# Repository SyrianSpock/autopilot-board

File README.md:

Speedy, the nanocopter
======================

The aim of this project is to design a board enabling the control of a small quadrotor (nanocopter) that can be tracked by external visual sensors.

### Specifications
* Cortex M4 MCU
* Four infrared LEDs on each side of the board for IR vision tracking. Each side can be controlled separately.
* Two full H bridges: one half bridge per motor to allow active braking of the motors.
* IMU:
    - MPU9250 (9 axis): accelerometer, gyroscope and magnetometer
    - MS5611 barometer
* Ground distance sensor:
    - ST VL53L0X for landing / ground approach
* Telemetry module:
    - ESP12E for telemetry and telecommand through WiFi
* USB interface (for DFU programming / serial interface) and power/charging
* Battery management unit
	- Monitor battery (current, voltage)
	- Supply power to the board from a LiPo (1S) input
	- Recharge the battery through USB

### PCB

The 40mm x 40mm board is rendered below

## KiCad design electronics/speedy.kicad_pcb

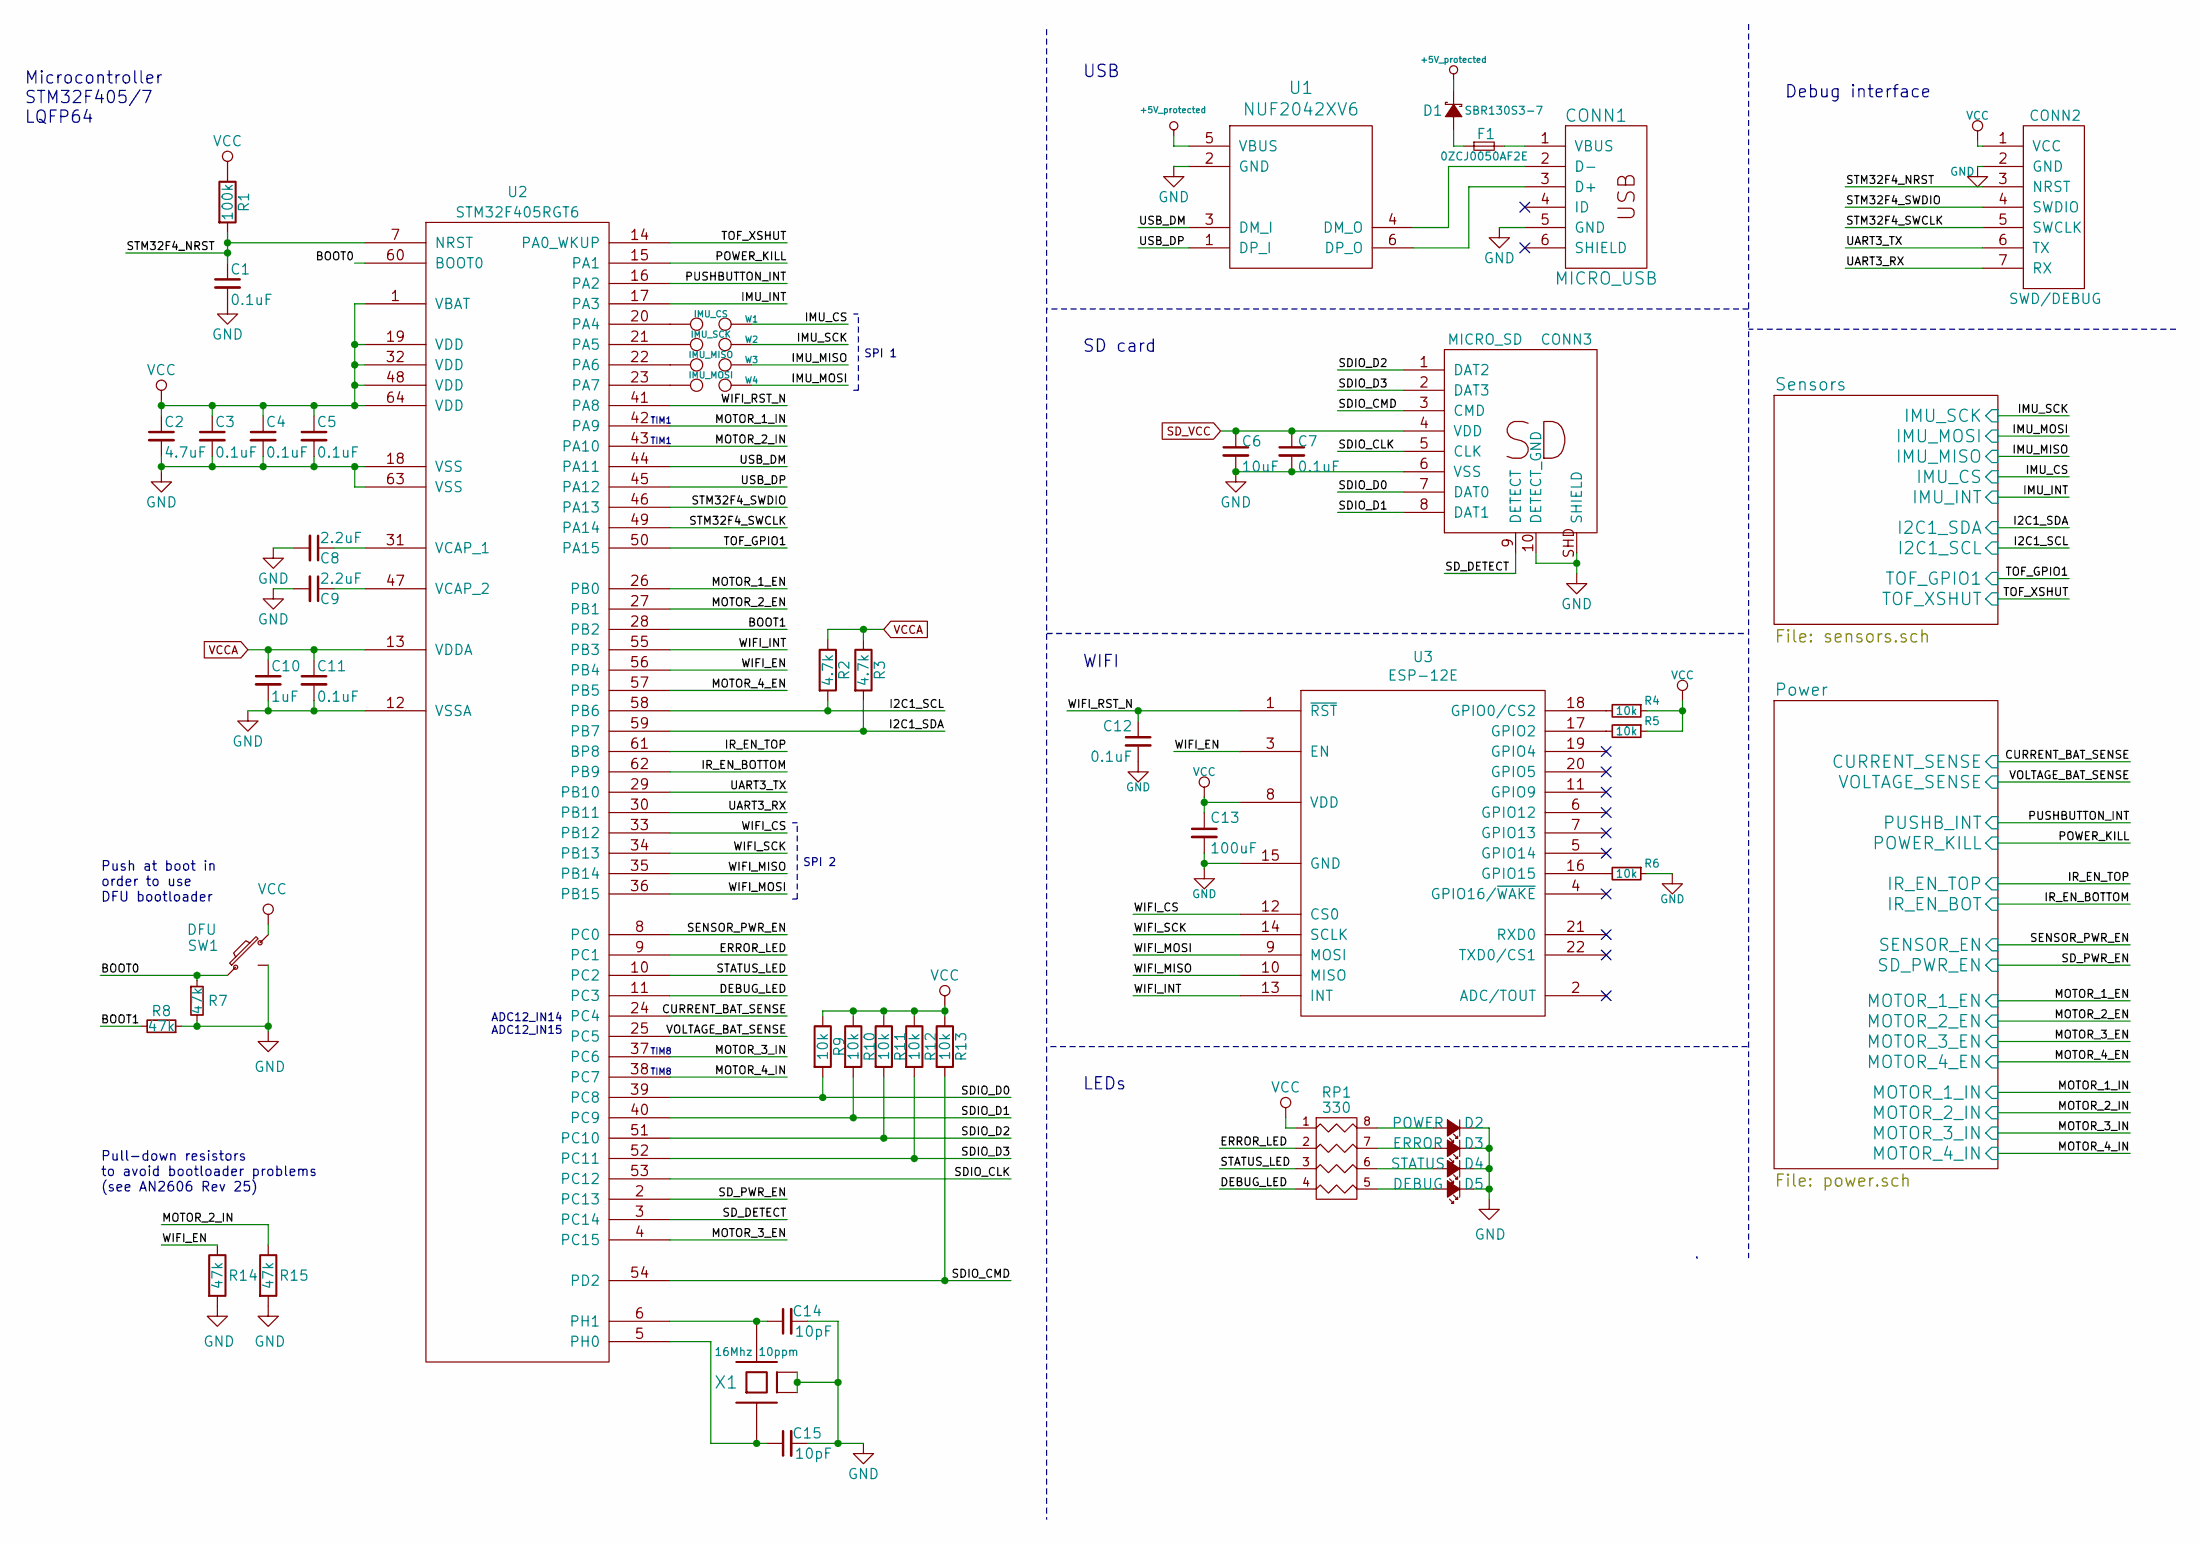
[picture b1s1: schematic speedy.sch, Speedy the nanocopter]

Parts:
C1, C3, C4, C5, C7, C11, C12: 0.1uF; _0402
C2: 4.7uF; _0402
C6: 10uF; _0603
C8, C9: 2.2uF; _0402
C10: 1uF; _0402
C13: 100uF; _0603
C14, C15: 10pF; _0402
CONN1: MICRO_USB; _Micro-USB-AB-receptacle-SMT-th
CONN2: SWD/DEBUG; _Molex-PicoBlade-SMD-7
CONN3: MICRO_SD; _Molex-microSD-502570-0893
D1: SBR130S3-7; _SOD-323
D2: POWER; _LED_0603
D3: ERROR; _LED_0603
D4: STATUS; _LED_0603
D5: DEBUG; _LED_0603
F1: 0ZCJ0050AF2E; _0402
R1: 100k; _0402
R2, R3: 4.7k; _0402
R4, R5, R6, R9, R10, R11, R12, R13: 10k; _0402
R7, R8, R14, R15: 47k; _0402
RP1: 330; R_Array_Concave_4x0402
SW1: DFU; SMD_Pushbutton_B3U-3100P
U1: NUF2042XV6; SOT-563_6-lead
U2: STM32F405RGT6; _LQFP64
U3: ESP-12E; ESP-12-E
W1: IMU_CS; TestPad
W2: IMU_SCK; TestPad
W3: IMU_MISO; TestPad
W4: IMU_MOSI; TestPad
X1: 16Mhz 10ppm; _TSX-3225-SMD-XTAL

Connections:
+5V_protected: D1.2 (C), U1.5 (VBUS); also elsewhere on the board
/BOOT0: R7.1, SW1.1, U2.60 (BOOT0)
/BOOT1: R8.2, U2.28 (PB2)
/CURRENT_BAT_SENSE: U2.24 (PC4); also elsewhere on the board
/I2C1_SCL: R2.2, U2.58 (PB6); also elsewhere on the board
/I2C1_SDA: R3.2, U2.59 (PB7); also elsewhere on the board
/IMU_CS: W1.2; also elsewhere on the board
/IMU_INT: U2.17 (PA3); also elsewhere on the board
/IMU_MISO: W3.2; also elsewhere on the board
/IMU_MOSI: W4.2; also elsewhere on the board
/IMU_SCK: W2.2; also elsewhere on the board
/IR_EN_TOP: U2.61 (BP8); also elsewhere on the board
/MOTOR_1_IN: U2.42 (PA9); also elsewhere on the board
/MOTOR_2_IN: R15.1, U2.43 (PA10); also elsewhere on the board
/MOTOR_3_EN: U2.4 (PC15); also elsewhere on the board
/MOTOR_3_IN: U2.37 (PC6); also elsewhere on the board
/MOTOR_4_IN: U2.38 (PC7); also elsewhere on the board
/POWER_KILL: U2.26 (PB0); also elsewhere on the board
/PUSHBUTTON_INT: U2.27 (PB1); also elsewhere on the board
/SDIO_CLK: CONN3.5 (CLK), U2.53 (PC12)
/SDIO_CMD: CONN3.3 (CMD), R13.2, U2.54 (PD2)
/SDIO_D0: CONN3.7 (DAT0), R9.2, U2.39 (PC8)
/SDIO_D1: CONN3.8 (DAT1), R10.2, U2.40 (PC9)
/SDIO_D2: CONN3.1 (DAT2), R11.2, U2.51 (PC10)
/SDIO_D3: CONN3.2 (DAT3), R12.2, U2.52 (PC11)
/SD_DETECT: CONN3.9 (DETECT), U2.3 (PC14)
/SD_PWR_EN: U2.2 (PC13); also elsewhere on the board
/SENSOR_PWR_EN: U2.8 (PC0); also elsewhere on the board
/STM32F4_NRST: C1.1, CONN2.3 (NRST), R1.2, U2.7 (NRST)
/STM32F4_SWCLK: CONN2.5 (SWCLK), U2.49 (PA14)
/STM32F4_SWDIO: CONN2.4 (SWDIO), U2.46 (PA13)
/TOF_GPIO1: U2.62 (PB9); also elsewhere on the board
/TOF_XSHUT: U2.57 (PB5); also elsewhere on the board
/UART3_RX: CONN2.7 (RX), U2.30 (PB11)
/UART3_TX: CONN2.6 (TX), U2.29 (PB10)
/USB_DM: U1.3 (DM_I), U2.44 (PA11)
/USB_DP: U1.1 (DP_I), U2.45 (PA12)
/VOLTAGE_BAT_SENSE: U2.25 (PC5); also elsewhere on the board
/WIFI_CS: U2.33 (PB12), U3.12 (CS0)
/WIFI_EN: R14.1, U2.56 (PB4), U3.3 (EN)
/WIFI_INT: U2.55 (PB3), U3.13 (INT)
/WIFI_MISO: U2.35 (PB14), U3.10 (MISO)
/WIFI_MOSI: U2.36 (PB15), U3.9 (MOSI)
/WIFI_SCK: U2.34 (PB13), U3.14 (SCLK)
GND: C1.2, C2.2, C3.2, C4.2, C5.2, C6.2, C7.2, C8.2, C9.2, C10.2, C11.2, C12.2, C13.2, C14.2, C15.2, CONN1.5 (GND), CONN2.2 (GND), CONN2.MECH (GND), CONN3.6 (VSS), CONN3.10 (DETECT_GND), CONN3.SHD (SHIELD), D2.1 (K), D3.1 (K), D4.1 (K), D5.1 (K), R6.1, R7.2, R8.1, R14.2, R15.2, SW1.3 (GND), U1.2 (GND), U2.12 (VSSA), U2.18 (VSS), U2.63 (VSS), U3.15 (GND), X1.2 (case), X1.4 (case); also elsewhere on the board
unnamed: C8.1, U2.31 (VCAP_1)
unnamed: C9.1, U2.47 (VCAP_2)
unnamed: C14.1, U2.6 (PH1), X1.3
unnamed: C15.1, U2.5 (PH0), X1.1
unnamed: CONN1.1 (VBUS), F1.2
unnamed: CONN1.2 (D-), U1.4 (DM_O)
unnamed: CONN1.3 (D+), U1.6 (DP_O)
unnamed: D1.1 (A), F1.1
unnamed: D2.2 (A), RP1.8 (R1)
unnamed: D3.2 (A), RP1.7 (R2)
unnamed: D4.2 (A), RP1.6 (R3)
unnamed: D5.2 (A), RP1.5 (R4)
unnamed: R4.2, U3.18 (GPIO0/CS2)
unnamed: R5.2, U3.17 (GPIO2)
unnamed: R6.2, U3.16 (GPIO15)
unnamed: U2.20 (PA4), W1.1
unnamed: U2.21 (PA5), W2.1
unnamed: U2.22 (PA6), W3.1
unnamed: U2.23 (PA7), W4.1
SD_VCC: C6.1, C7.1, CONN3.4 (VDD); also elsewhere on the board
VCC: C2.1, C3.1, C4.1, C5.1, C13.1, CONN2.1 (VCC), R1.1, R4.1, R5.1, R9.1, R10.1, R11.1, R12.1, R13.1, RP1.1, SW1.2, U2.1 (VBAT), U2.19 (VDD), U2.32 (VDD), U2.48 (VDD), U2.64 (VDD), U3.8 (VDD); also elsewhere on the board

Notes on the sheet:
SPI 2
ADC12_IN14 ADC12_IN15
Microcontroller STM32F405/7 LQFP64
SD card
Debug interface
USB
LEDs
Push at boot in order to use DFU bootloader
TIM8
TIM1
Pull-down resistors to avoid bootloader problems (see AN2606 Rev 25)
SPI 1
WIFI

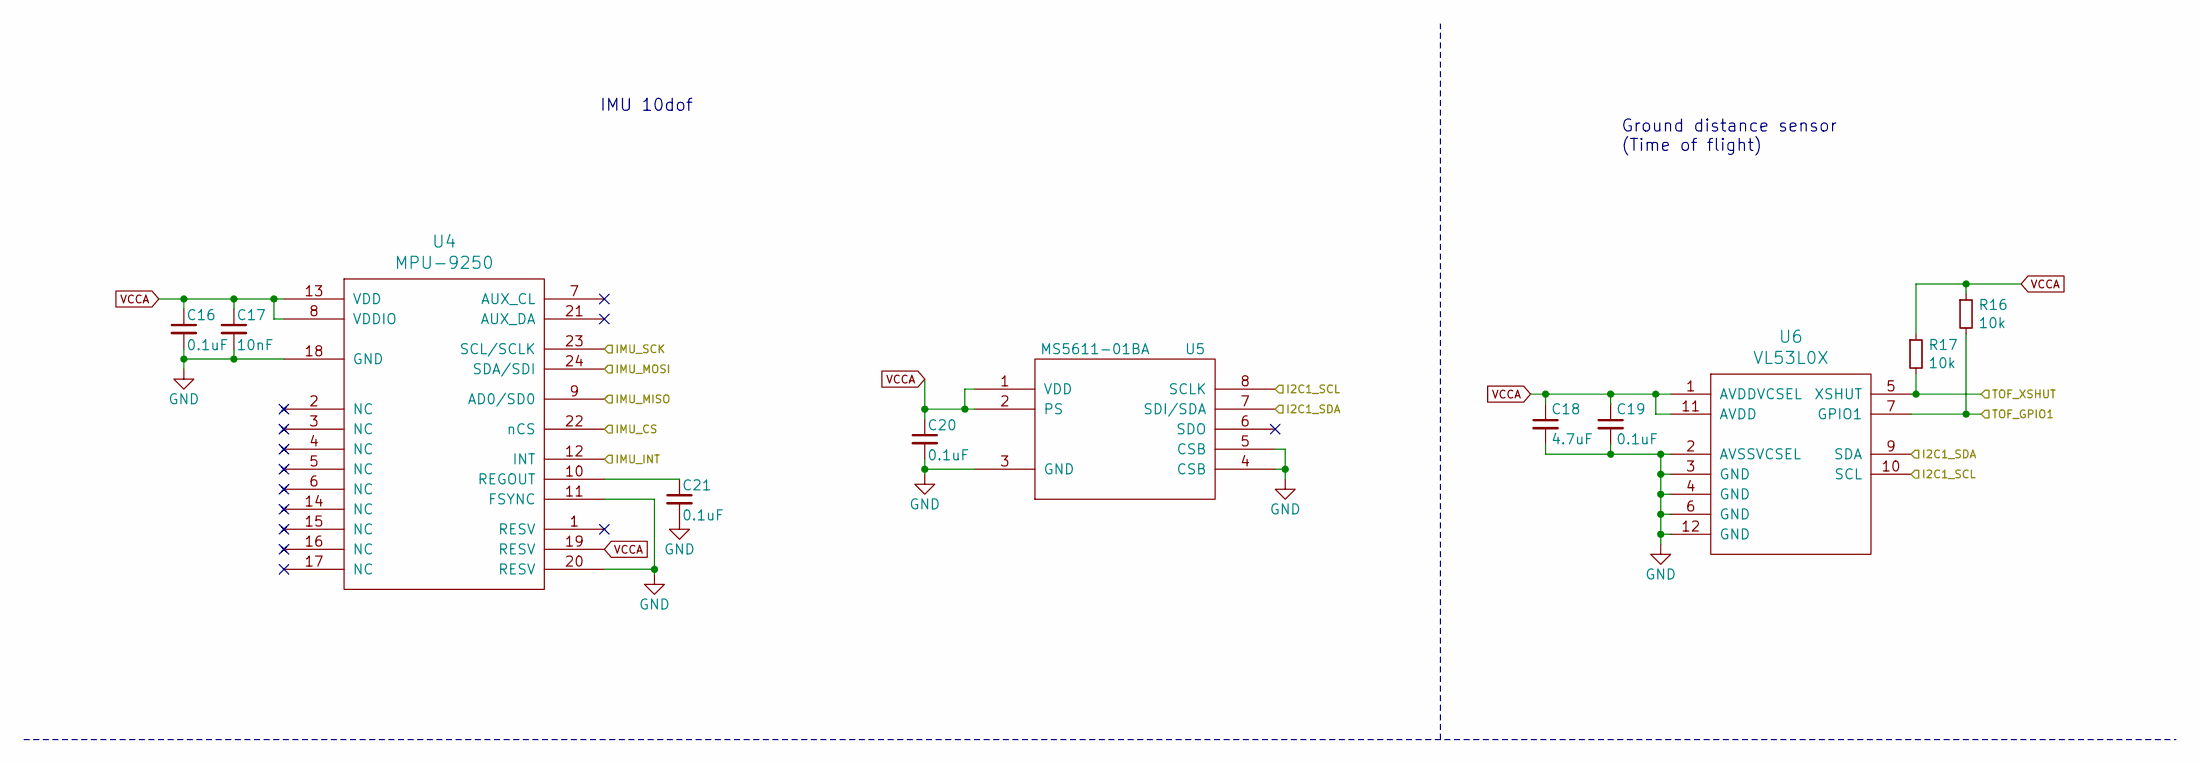
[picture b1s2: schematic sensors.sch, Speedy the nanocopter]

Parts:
C16, C19, C20, C21: 0.1uF; _0402
C17: 10nF; _0402
C18: 4.7uF; _0402
R16, R17: 10k; _0402
U4: MPU-9250; _MPU-9XX0
U5: MS5611-01BA; _MS5611-01BA
U6: VL53L0X; ST-VL53L0X

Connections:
/I2C1_SCL: U5.8 (SCLK), U6.10 (SCL); also elsewhere on the board
/I2C1_SDA: U5.7 (SDI/SDA), U6.9 (SDA); also elsewhere on the board
/IMU_CS: U4.22 (nCS); also elsewhere on the board
/IMU_INT: U4.12 (INT); also elsewhere on the board
/IMU_MISO: U4.9 (AD0/SD0); also elsewhere on the board
/IMU_MOSI: U4.24 (SDA/SDI); also elsewhere on the board
/IMU_SCK: U4.23 (SCL/SCLK); also elsewhere on the board
/TOF_GPIO1: R16.2, U6.7 (GPIO1); also elsewhere on the board
/TOF_XSHUT: R17.2, U6.5 (XSHUT); also elsewhere on the board
GND: C16.2, C17.2, C18.2, C19.2, C20.2, C21.2, U4.11 (FSYNC), U4.18 (GND), U4.20 (RESV), U5.3 (GND), U5.4 (CSB), U5.5 (CSB), U6.2 (AVSSVCSEL), U6.3 (GND), U6.4 (GND), U6.6 (GND), U6.12 (GND); also elsewhere on the board
unnamed: C21.1, U4.10 (REGOUT)

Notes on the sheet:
Ground distance sensor (Time of flight)
IMU 10dof

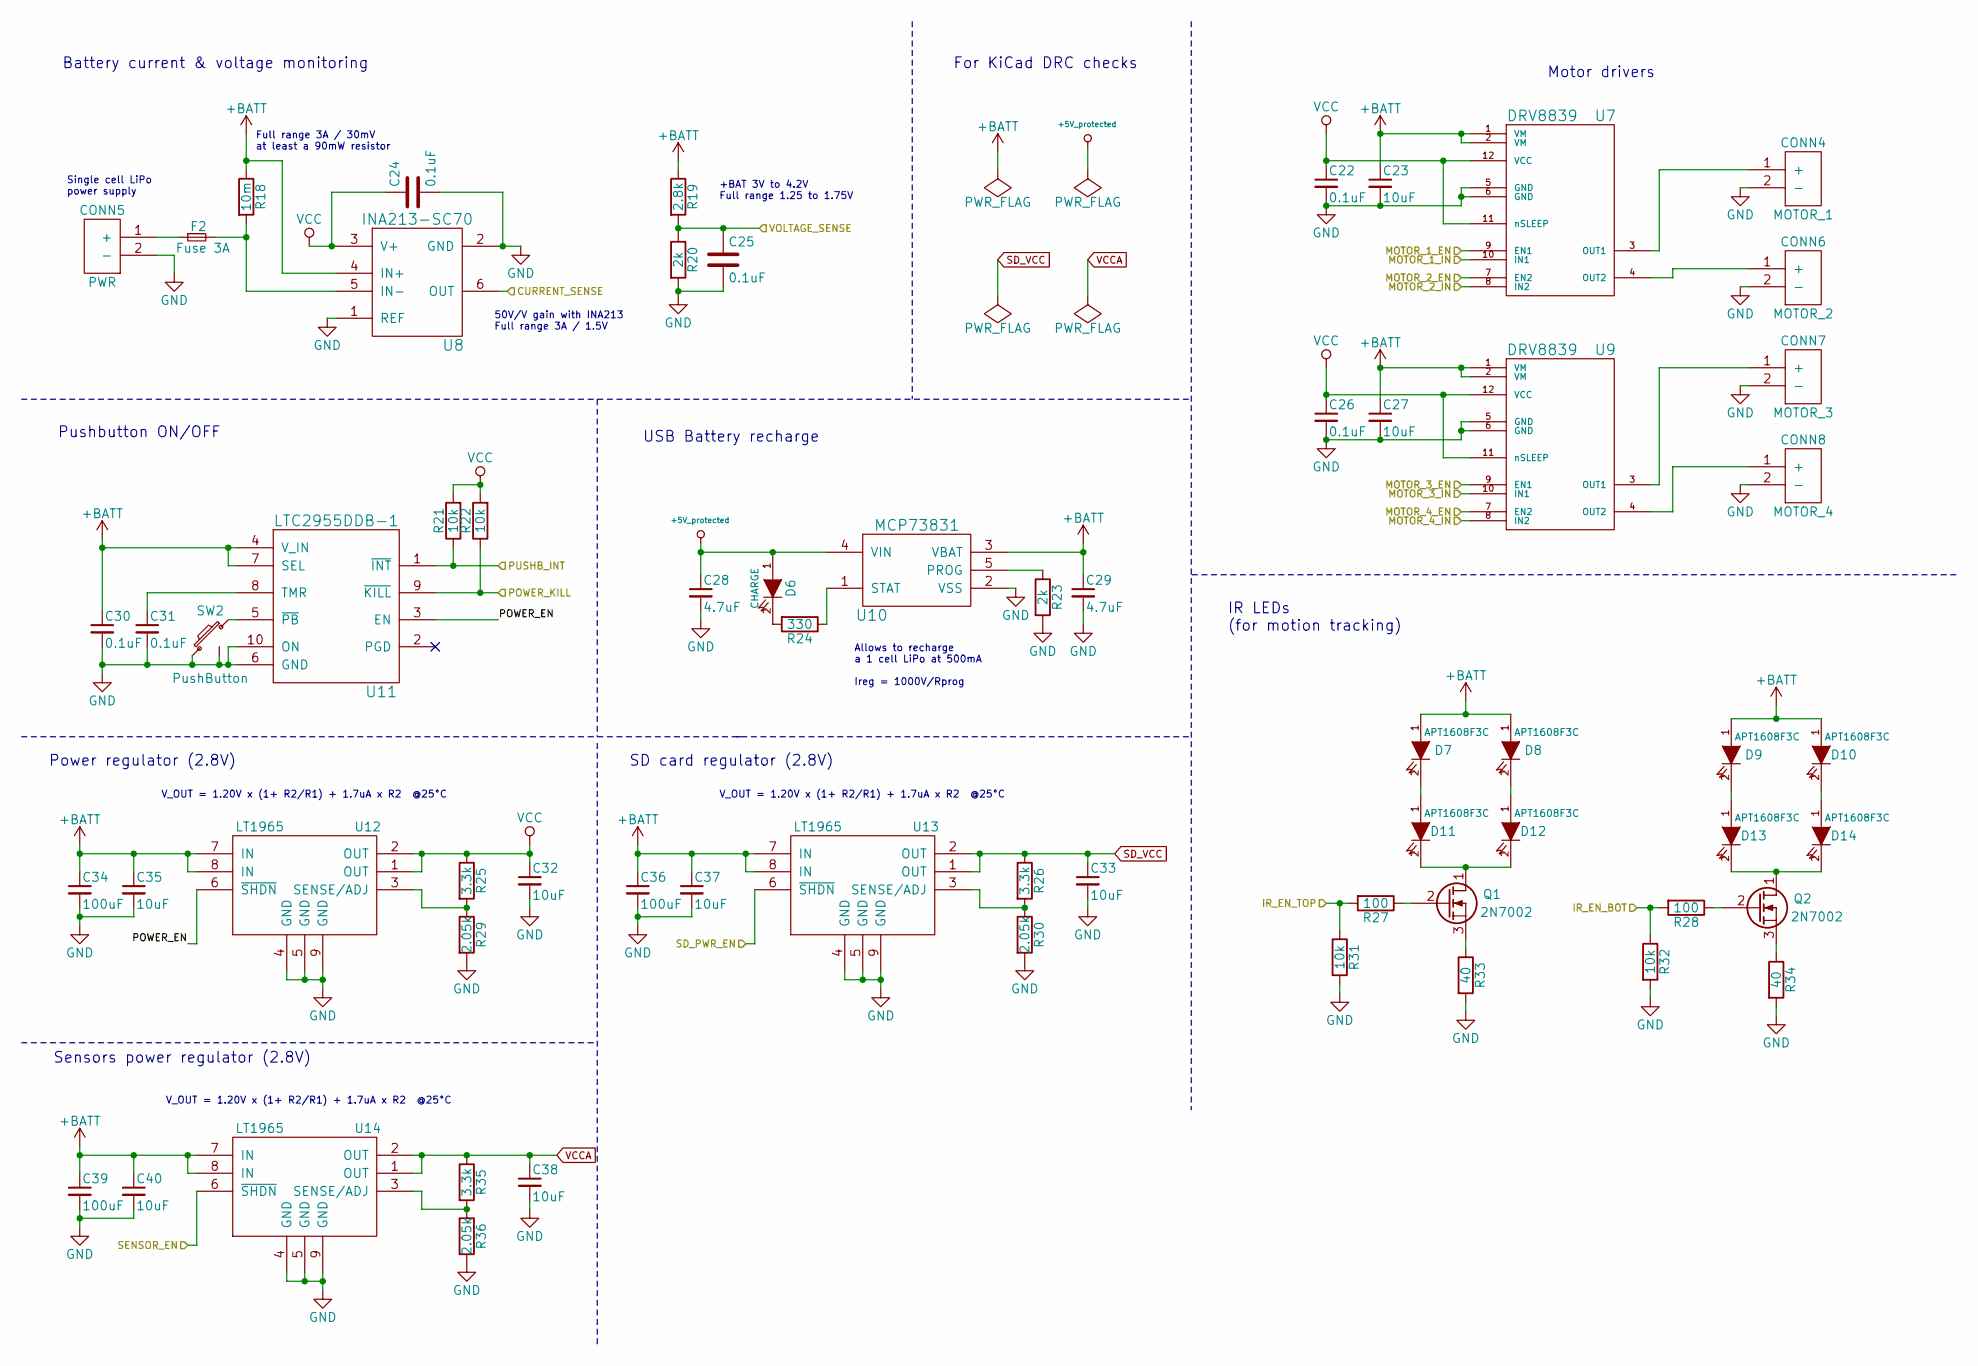
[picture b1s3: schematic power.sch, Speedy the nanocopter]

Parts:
C22, C24, C25, C26, C30, C31: 0.1uF; _0402
C23, C27, C32, C33, C35, C37, C38, C40: 10uF; _0603
C28, C29: 4.7uF; _0402
C34, C36, C39: 100uF; _0603
CONN4: MOTOR_1; _Solder_Pad1.27_2
CONN5: PWR; _Pin2mm_2
CONN6: MOTOR_2; _Solder_Pad1.27_2
CONN7: MOTOR_3; _Solder_Pad1.27_2
CONN8: MOTOR_4; _Solder_Pad1.27_2
D6: CHARGE; _LED_0603
D7, D8, D9, D10, D11, D12, D13, D14: APT1608F3C; _LED_0603
F2: Fuse 3A; _0402
Q1, Q2: 2N7002; _SOT23-3
R18: 10m; _0402
R19: 2.8k; _0402
R20, R23: 2k; _0402
R21, R22, R31, R32: 10k; _0402
R24: 330; _0402
R25, R26, R35: 3.3k; _0402
R27, R28: 100; _0402
R29, R30, R36: 2.05k; _0402
R33, R34: 40; _0402
SW2: PushButton; SMD_Pushbutton_B3U-3100P
U7, U9: DRV8839; TI-DRV8839_PWSON-N12
U8: INA213-SC70; SC70
U10: MCP73831; _TSOT23-5
U11: LTC2955DDB-1; DFN-10-1EP_2x3mm_Pitch0.5mm
U12, U13, U14: LT1965; DFN-8-1EP_3x3mm_Pitch0.5mm

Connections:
+5V_protected: C28.1, D6.1 (A), U10.4 (VIN); also elsewhere on the board
+BATT: C23.1, C27.1, C29.1, C30.1, C34.1, C35.1, C36.1, C37.1, C39.1, C40.1, D7.1 (A), D8.1 (A), D9.1 (A), D10.1 (A), R18.1, R19.1, U7.1 (VM), U7.2 (VM), U8.4 (IN+), U9.1 (VM), U9.2 (VM), U10.3 (VBAT), U11.4 (V_IN), U11.7 (SEL), U12.7 (IN), U12.8 (IN), U13.7 (IN), U13.8 (IN), U14.7 (IN), U14.8 (IN)
/CURRENT_BAT_SENSE: U8.6 (OUT); also elsewhere on the board
/IR_EN_TOP: R27.2, R31.1; also elsewhere on the board
/MOTOR_1_IN: U7.10 (IN1); also elsewhere on the board
/MOTOR_2_IN: U7.8 (IN2); also elsewhere on the board
/MOTOR_3_EN: U9.9 (EN1); also elsewhere on the board
/MOTOR_3_IN: U9.10 (IN1); also elsewhere on the board
/MOTOR_4_IN: U9.8 (IN2); also elsewhere on the board
/POWER_KILL: R22.1, U11.9 (~KILL); also elsewhere on the board
/PUSHBUTTON_INT: R21.1, U11.1 (~INT); also elsewhere on the board
/Power/POWER_EN: U11.3 (EN), U12.6 (~SHDN)
/SD_PWR_EN: U13.6 (~SHDN); also elsewhere on the board
/SENSOR_PWR_EN: U14.6 (~SHDN); also elsewhere on the board
/VOLTAGE_BAT_SENSE: C25.1, R19.2, R20.1; also elsewhere on the board
GND: C22.2, C23.2, C24.2, C25.2, C26.2, C27.2, C28.2, C29.2, C30.2, C31.2, C32.2, C33.2, C34.2, C35.2, C36.2, C37.2, C38.2, C39.2, C40.2, CONN4.2 (-), CONN5.2 (-), CONN6.2 (-), CONN7.2 (-), CONN8.2 (-), R20.2, R23.2, R29.2, R30.2, R31.2, R32.2, R33.2, R34.2, R36.2, SW2.2, SW2.3 (GND), U7.5 (GND), U7.6 (GND), U7.THRM, U8.1 (REF), U8.2 (GND), U9.5 (GND), U9.6 (GND), U9.THRM, U10.2 (VSS), U11.6 (GND), U11.10 (ON), U12.4 (GND), U12.5 (GND), U12.9 (GND), U13.4 (GND), U13.5 (GND), U13.9 (GND), U14.4 (GND), U14.5 (GND), U14.9 (GND); also elsewhere on the board
unnamed: C31.1, U11.8 (TMR)
unnamed: CONN4.1 (+), U7.3 (OUT1)
unnamed: CONN5.1 (+), F2.1
unnamed: CONN6.1 (+), U7.4 (OUT2)
unnamed: CONN7.1 (+), U9.3 (OUT1)
unnamed: CONN8.1 (+), U9.4 (OUT2)
unnamed: D6.2 (K), R24.2
unnamed: D10.2 (K), D14.1 (A)
unnamed: D7.2 (K), D11.1 (A)
unnamed: D11.2 (K), D12.2 (K), Q1.1 (D)
unnamed: D8.2 (K), D12.1 (A)
unnamed: D9.2 (K), D13.1 (A)
unnamed: D13.2 (K), D14.2 (K), Q2.1 (D)
unnamed: F2.2, R18.2, U8.5 (IN-)
unnamed: Q1.2 (G), R27.1
unnamed: Q1.3 (S), R33.1
unnamed: Q2.2 (G), R28.1
unnamed: Q2.3 (S), R34.1
unnamed: R23.1, U10.5 (PROG)
unnamed: R24.1, U10.1 (STAT)
unnamed: R25.2, R29.1, U12.3 (SENSE/ADJ)
unnamed: R26.2, R30.1, U13.3 (SENSE/ADJ)
unnamed: R35.2, R36.1, U14.3 (SENSE/ADJ)
unnamed: SW2.1, U11.5 (~PB)
SD_VCC: C33.1, R26.1, U13.1 (OUT), U13.2 (OUT); also elsewhere on the board
VCC: C22.1, C24.1, C26.1, C32.1, R21.2, R22.2, R25.1, U7.11 (nSLEEP), U7.12 (VCC), U8.3 (V+), U9.11 (nSLEEP), U9.12 (VCC), U12.1 (OUT), U12.2 (OUT); also elsewhere on the board

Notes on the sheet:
Allows to recharge a 1 cell LiPo at 500mA Ireg = 1000V/Rprog
V_OUT = 1.20V x (1+ R2/R1) + 1.7uA x R2 @25°C
Single cell LiPo power supply
Full range 3A / 30mV at least a 90mW resistor
50V/V gain with INA213 Full range 3A / 1.5V
+BAT 3V to 4.2V Full range 1.25 to 1.75V
Battery current & voltage monitoring
Power regulator (2.8V)
Pushbutton ON/OFF
USB Battery recharge
Motor drivers
IR LEDs (for motion tracking)
For KiCad DRC checks
Sensors power regulator (2.8V)
SD card regulator (2.8V)

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
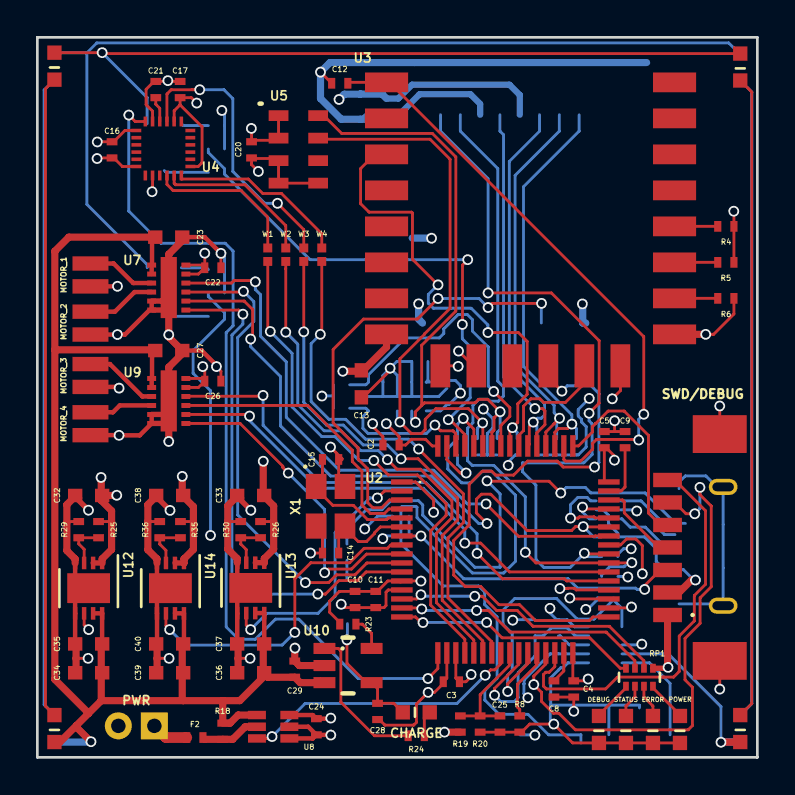
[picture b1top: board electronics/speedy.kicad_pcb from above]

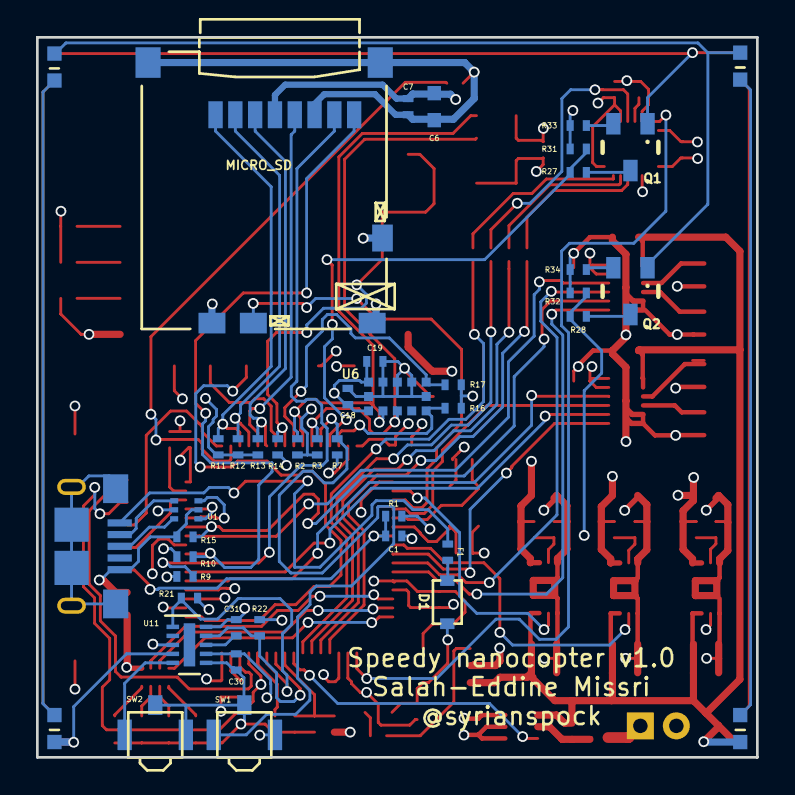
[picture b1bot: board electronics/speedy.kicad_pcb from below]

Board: 4 copper layers, 40.0 x 40.0 mm, 124 parts (43 on the bottom side), 102 nets.

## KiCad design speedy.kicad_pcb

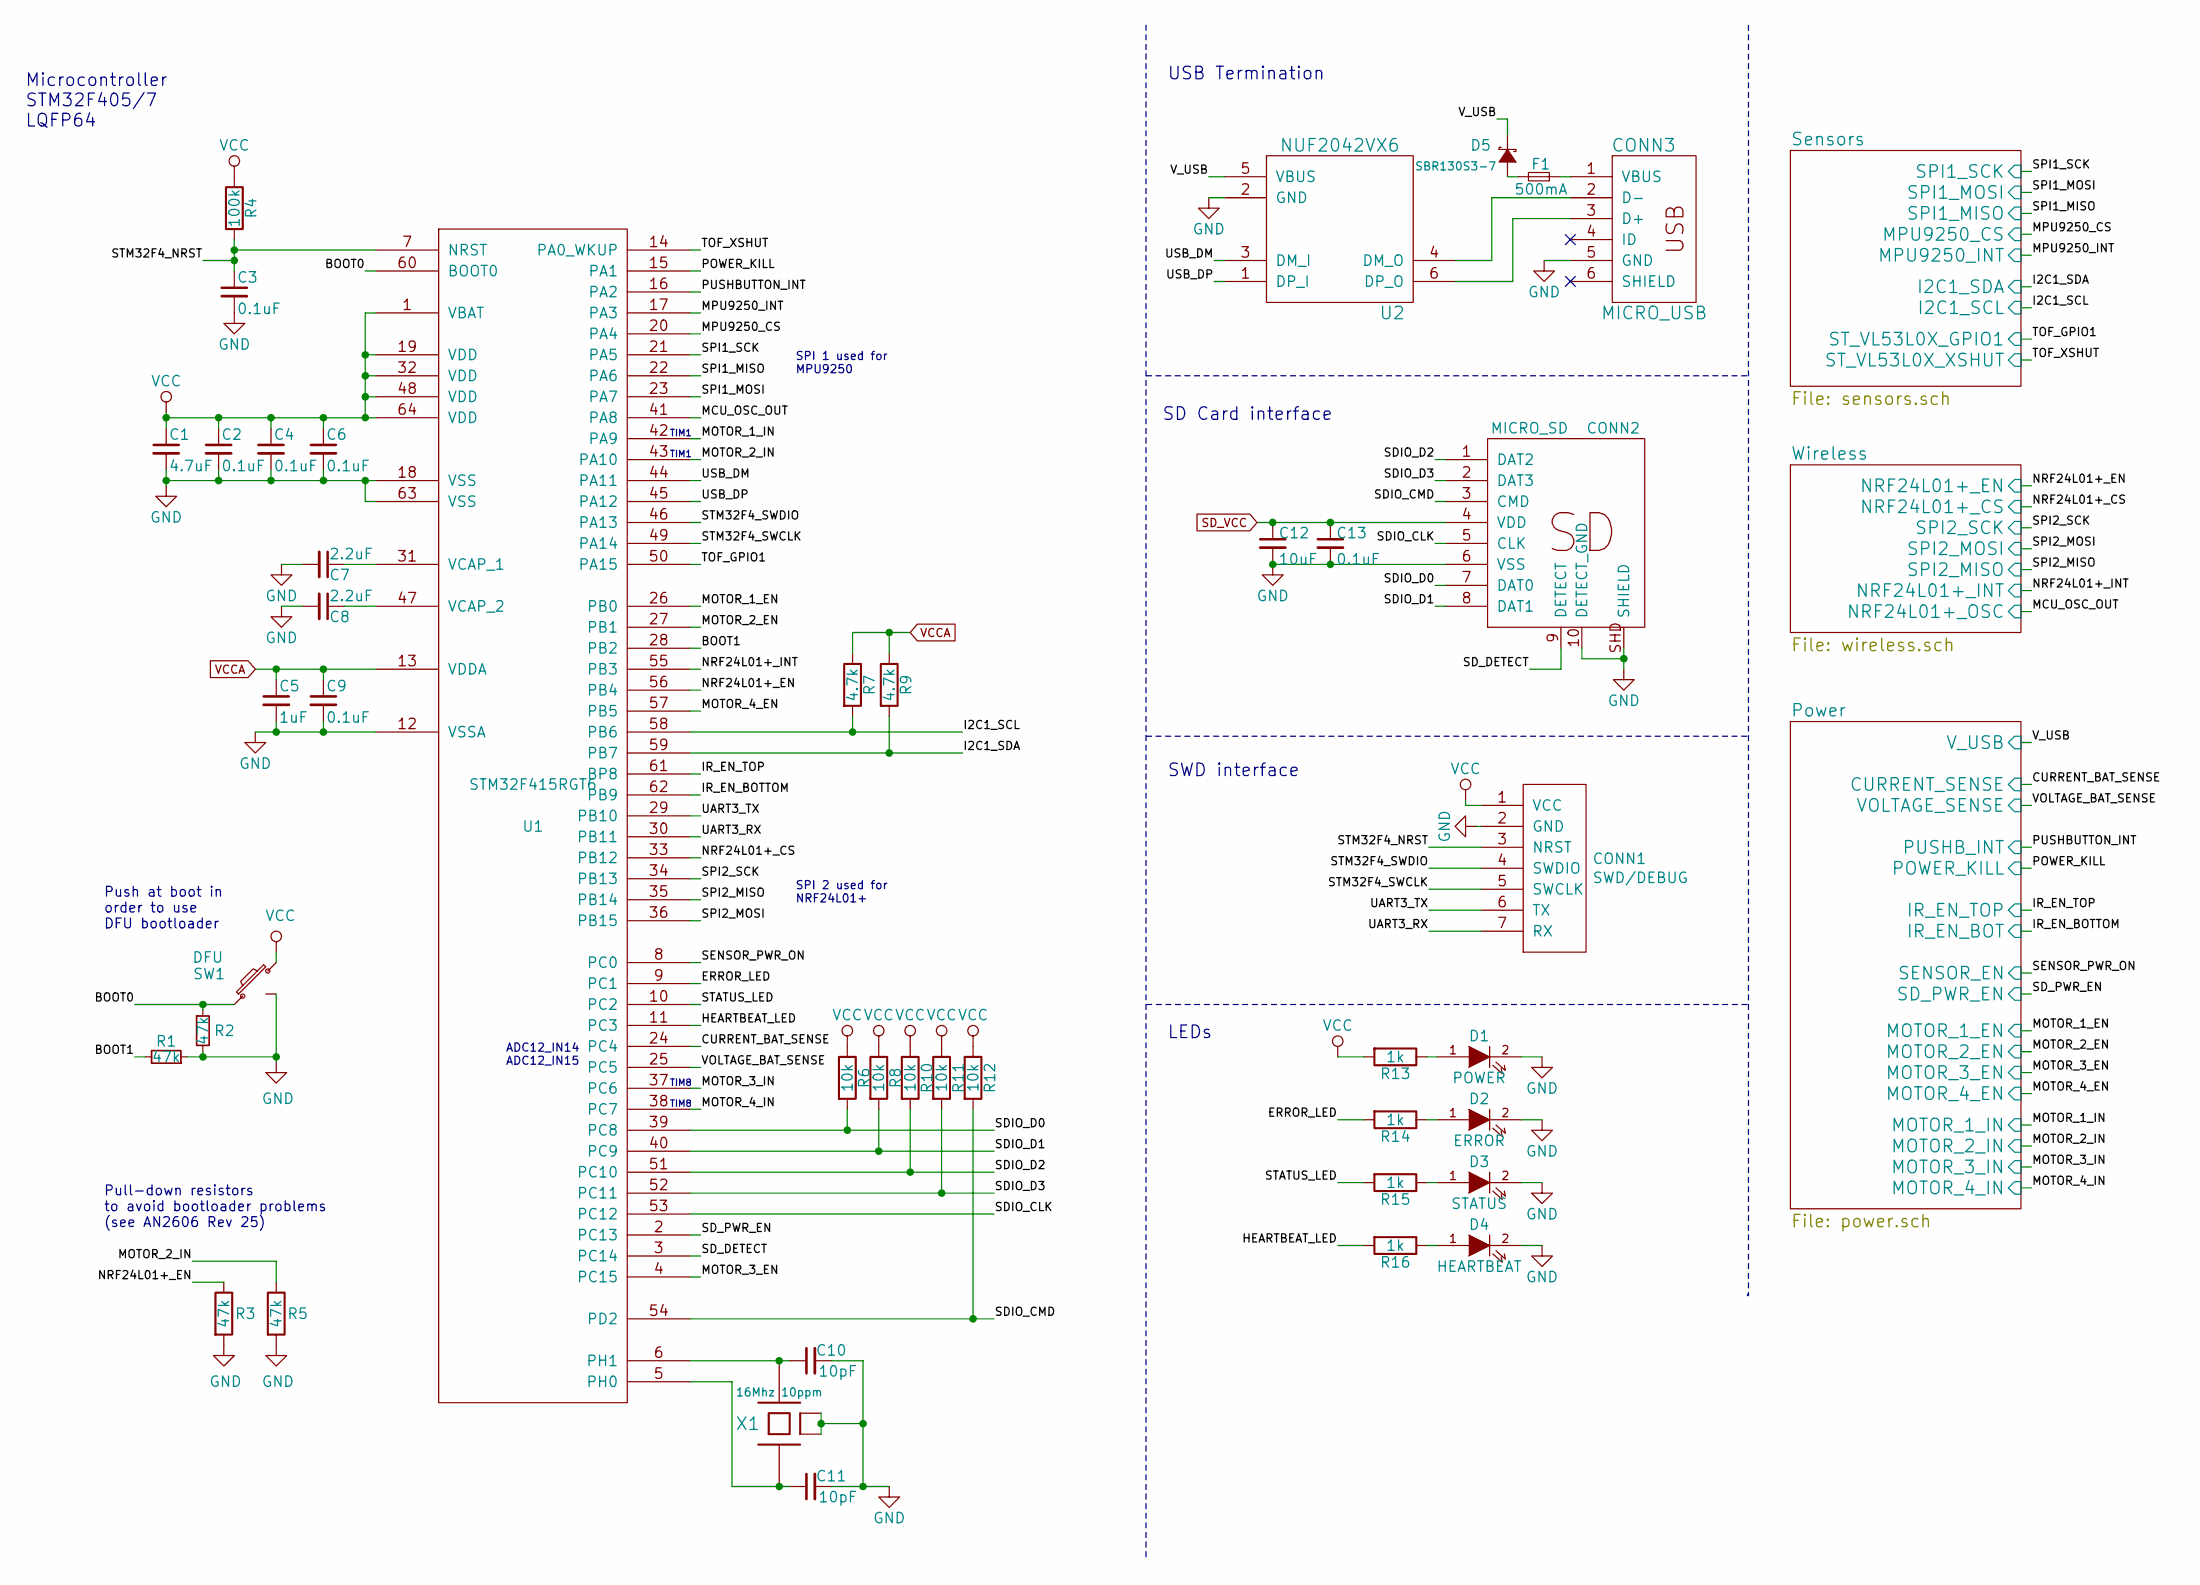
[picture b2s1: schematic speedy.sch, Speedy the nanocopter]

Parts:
C1: 4.7uF; _0402
C2, C3, C4, C6, C9, C13: 0.1uF; _0402
C5: 1uF; _0402
C7, C8: 2.2uF; _0402
C10, C11: 10pF; _0402
C12: 10uF; _0603
CONN1: SWD/DEBUG; _Molex-PicoBlade-SMD-7
CONN2: MICRO_SD; _Molex-microSD-WM6701
CONN3: MICRO_USB; _Micro-USB-AB-receptacle-SMT-th
D1: POWER; _LED_0603
D2: ERROR; _LED_0603
D3: STATUS; _LED_0603
D4: HEARTBEAT; _LED_0603
D5: SBR130S3-7; _SOD-323
F1: 500mA; _0402
R1, R2, R3, R5: 47k; _0402
R4: 100k; _0402
R6, R8, R10, R11, R12: 10k; _0402
R7, R9: 4.7k; _0402
R13, R14, R15, R16: 1k; _0402
SW1: DFU; SMD_Pushbutton_B3U-3100P
U1: STM32F415RGT6; _LQFP64
U2: NUF2042VX6; SOT-563_6-lead
X1: 16Mhz 10ppm; _TSX-3225-SMD-XTAL

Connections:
/BOOT0: R2.1, SW1.1, U1.60 (BOOT0)
/BOOT1: R1.2, U1.28 (PB2)
/CURRENT_BAT_SENSE: U1.24 (PC4); also elsewhere on the board
/ERROR_LED: R14.2, U1.9 (PC1)
/HEARTBEAT_LED: R16.2, U1.11 (PC3)
/I2C1_SCL: R7.2, U1.58 (PB6); also elsewhere on the board
/I2C1_SDA: R9.2, U1.59 (PB7); also elsewhere on the board
/IR_EN_BOTTOM: U1.62 (PB9); also elsewhere on the board
/IR_EN_TOP: U1.61 (BP8); also elsewhere on the board
/MCU_OSC_OUT: U1.41 (PA8); also elsewhere on the board
/MOTOR_1_EN: U1.26 (PB0); also elsewhere on the board
/MOTOR_1_IN: U1.42 (PA9); also elsewhere on the board
/MOTOR_2_EN: U1.27 (PB1); also elsewhere on the board
/MOTOR_2_IN: R5.1, U1.43 (PA10); also elsewhere on the board
/MOTOR_3_EN: U1.4 (PC15); also elsewhere on the board
/MOTOR_3_IN: U1.37 (PC6); also elsewhere on the board
/MOTOR_4_EN: U1.57 (PB5); also elsewhere on the board
/MOTOR_4_IN: U1.38 (PC7); also elsewhere on the board
/MPU9250_CS: U1.20 (PA4); also elsewhere on the board
/MPU9250_INT: U1.17 (PA3); also elsewhere on the board
/NRF24L01+_CS: U1.33 (PB12); also elsewhere on the board
/NRF24L01+_EN: R3.1, U1.56 (PB4); also elsewhere on the board
/NRF24L01+_INT: U1.55 (PB3); also elsewhere on the board
/POWER_KILL: U1.15 (PA1); also elsewhere on the board
/PUSHBUTTON_INT: U1.16 (PA2); also elsewhere on the board
/SDIO_CLK: CONN2.5 (CLK), U1.53 (PC12)
/SDIO_CMD: CONN2.3 (CMD), R12.2, U1.54 (PD2)
/SDIO_D0: CONN2.7 (DAT0), R6.2, U1.39 (PC8)
/SDIO_D1: CONN2.8 (DAT1), R8.2, U1.40 (PC9)
/SDIO_D2: CONN2.1 (DAT2), R10.2, U1.51 (PC10)
/SDIO_D3: CONN2.2 (DAT3), R11.2, U1.52 (PC11)
/SD_DETECT: CONN2.9 (DETECT), U1.3 (PC14)
/SD_PWR_EN: U1.2 (PC13); also elsewhere on the board
/SENSOR_PWR_ON: U1.8 (PC0); also elsewhere on the board
/SPI1_MISO: U1.22 (PA6); also elsewhere on the board
/SPI1_MOSI: U1.23 (PA7); also elsewhere on the board
/SPI1_SCK: U1.21 (PA5); also elsewhere on the board
/SPI2_MISO: U1.35 (PB14); also elsewhere on the board
/SPI2_MOSI: U1.36 (PB15); also elsewhere on the board
/SPI2_SCK: U1.34 (PB13); also elsewhere on the board
/STATUS_LED: R15.2, U1.10 (PC2)
/STM32F4_NRST: C3.1, CONN1.3 (NRST), R4.2, U1.7 (NRST)
/STM32F4_SWCLK: CONN1.5 (SWCLK), U1.49 (PA14)
/STM32F4_SWDIO: CONN1.4 (SWDIO), U1.46 (PA13)
/TOF_GPIO1: U1.50 (PA15); also elsewhere on the board
/TOF_XSHUT: U1.14 (PA0_WKUP); also elsewhere on the board
/UART3_RX: CONN1.7 (RX), U1.30 (PB11)
/UART3_TX: CONN1.6 (TX), U1.29 (PB10)
/USB_DM: U1.44 (PA11), U2.3 (DM_I)
/USB_DP: U1.45 (PA12), U2.1 (DP_I)
/VOLTAGE_BAT_SENSE: U1.25 (PC5); also elsewhere on the board
/V_USB: D5.2 (C), U2.5 (VBUS); also elsewhere on the board
GND: C1.2, C2.2, C3.2, C4.2, C5.2, C6.2, C7.2, C8.2, C9.2, C10.2, C11.2, C12.2, C13.2, CONN1.2 (GND), CONN1.MECH (GND), CONN2.6 (VSS), CONN2.10 (DETECT_GND), CONN2.SHD (SHIELD), CONN3.5 (GND), D1.2 (K), D2.2 (K), D3.2 (K), D4.2 (K), R1.1, R2.2, R3.2, R5.2, SW1.3 (GND), U1.12 (VSSA), U1.18 (VSS), U1.63 (VSS), U2.2 (GND), X1.2 (case), X1.4 (case); also elsewhere on the board
unnamed: C7.1, U1.31 (VCAP_1)
unnamed: C8.1, U1.47 (VCAP_2)
unnamed: C10.1, U1.6 (PH1), X1.3
unnamed: C11.1, U1.5 (PH0), X1.1
unnamed: CONN3.1 (VBUS), F1.2
unnamed: CONN3.2 (D-), U2.4 (DM_O)
unnamed: CONN3.3 (D+), U2.6 (DP_O)
unnamed: D1.1 (A), R13.1
unnamed: D2.1 (A), R14.1
unnamed: D3.1 (A), R15.1
unnamed: D4.1 (A), R16.1
unnamed: D5.1 (A), F1.1
SD_VCC: C12.1, C13.1, CONN2.4 (VDD); also elsewhere on the board
VCC: C1.1, C2.1, C4.1, C6.1, CONN1.1 (VCC), R4.1, R6.1, R8.1, R10.1, R11.1, R12.1, R13.2, SW1.2, U1.1 (VBAT), U1.19 (VDD), U1.32 (VDD), U1.48 (VDD), U1.64 (VDD); also elsewhere on the board
VCCA: C5.1, C9.1, R7.1, R9.1, U1.13 (VDDA); also elsewhere on the board

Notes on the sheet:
SPI 1 used for MPU9250
SPI 2 used for NRF24L01+
ADC12_IN14 ADC12_IN15
Microcontroller STM32F405/7 LQFP64
SD Card interface
SWD interface
USB Termination
LEDs
Push at boot in order to use DFU bootloader
TIM8
TIM1
Pull-down resistors to avoid bootloader problems (see AN2606 Rev 25)

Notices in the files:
electronics/power.sch:
License: CC-BY 4.0
